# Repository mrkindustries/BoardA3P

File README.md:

BoardA3PU
=============

## Arduino-compatible FPGA board

## Schematic

## 3D views

This board was designed using kicad, you can find the CAD files in the /hardware/design folder
http://www.kicad-pcb.org

Download the schematic

[schematic.pdf](/hardware/doc/schematic.pdf?raw=true)

**Warning:** untested until the first prototype arrives

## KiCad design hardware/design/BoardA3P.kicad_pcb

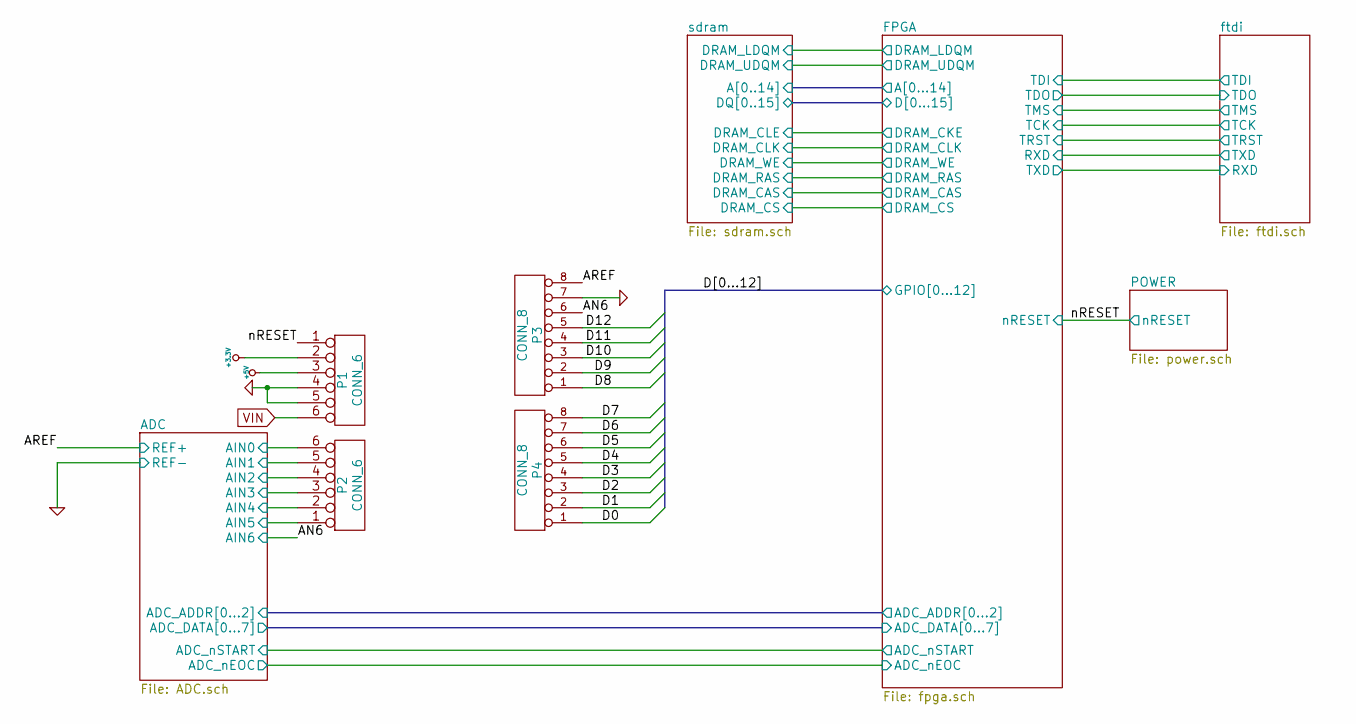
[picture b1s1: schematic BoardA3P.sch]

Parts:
P1, P2: CONN_6; SIL-6
P3, P4: CONN_8; SIL-8

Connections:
+3.3V: P1.2; also elsewhere on the board
+5V: P1.3; also elsewhere on the board
/ADC/AIN0: P2.6; also elsewhere on the board
/ADC/AIN1: P2.5; also elsewhere on the board
/ADC/AIN2: P2.4; also elsewhere on the board
/ADC/AIN3: P2.3; also elsewhere on the board
/ADC/AIN4: P2.2; also elsewhere on the board
/ADC/AIN5: P2.1; also elsewhere on the board
/ADC/AIN6: P3.6; also elsewhere on the board
/ADC/REF+: P3.8; also elsewhere on the board
/D0: P4.1; also elsewhere on the board
/D1: P4.2; also elsewhere on the board
/D2: P4.3; also elsewhere on the board
/D3: P4.4; also elsewhere on the board
/D4: P4.5; also elsewhere on the board
/D5: P4.6; also elsewhere on the board
/D6: P4.7; also elsewhere on the board
/D7: P4.8; also elsewhere on the board
/D8: P3.1; also elsewhere on the board
/D9: P3.2; also elsewhere on the board
/D10: P3.3; also elsewhere on the board
/D11: P3.4; also elsewhere on the board
/D12: P3.5; also elsewhere on the board
/FPGA/nRESET: P1.1; also elsewhere on the board
GND: P1.4, P1.5, P3.7; also elsewhere on the board
VIN: P1.6; also elsewhere on the board

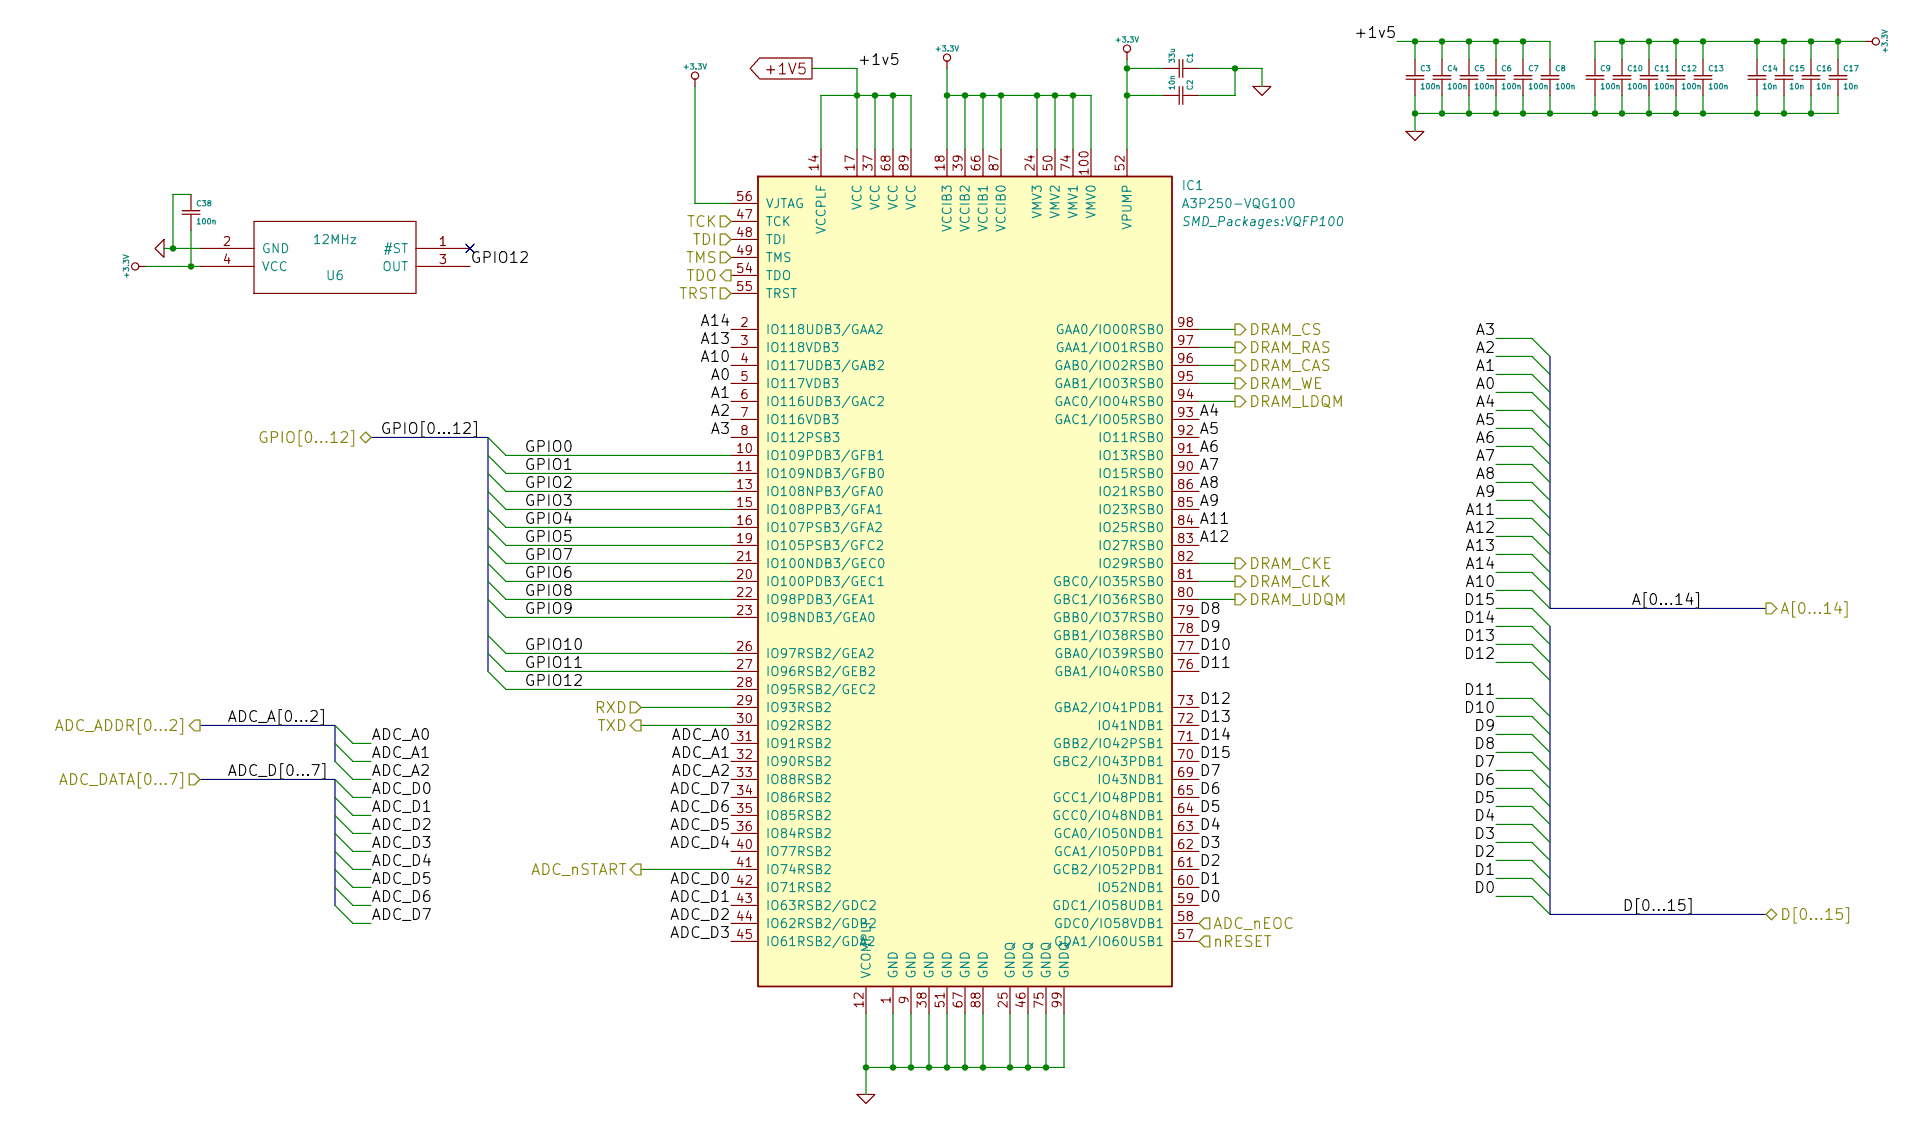
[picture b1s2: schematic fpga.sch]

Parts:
C1: 33u; c_0805
C2, C14, C15, C16, C17: 10n; c_0805
C3, C4, C5, C6, C7, C8, C9, C10, C11, C12, C13, C38: 100n; c_0805
IC1: A3P250-VQG100; VQFP100
U6: 12MHz; OSC_2x2p5

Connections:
+1V5: C3.1, C4.1, C5.1, C6.1, C7.1, C8.1, IC1.14 (VCCPLF), IC1.17 (VCC), IC1.37 (VCC), IC1.68 (VCC), IC1.89 (VCC); also elsewhere on the board
+3.3V: C1.2, C2.2, C9.1, C10.1, C11.1, C12.1, C13.1, C14.1, C15.1, C16.1, C17.1, C38.2, IC1.18 (VCCIB3), IC1.24 (VMV3), IC1.39 (VCCIB2), IC1.50 (VMV2), IC1.52 (VPUMP), IC1.56 (VJTAG), IC1.66 (VCCIB1), IC1.74 (VMV1), IC1.87 (VCCIB0), IC1.100 (VMV0), U6.4 (VCC); also elsewhere on the board
/ADC/A0: IC1.31 (IO91RSB2); also elsewhere on the board
/ADC/A1: IC1.32 (IO90RSB2); also elsewhere on the board
/ADC/A2: IC1.33 (IO88RSB2); also elsewhere on the board
/ADC/ADC_nEOC: IC1.58 (GDC0/IO58VDB1); also elsewhere on the board
/ADC/ADC_nSTART: IC1.41 (IO74RSB2); also elsewhere on the board
/D0: IC1.10 (IO109PDB3/GFB1); also elsewhere on the board
/D1: IC1.11 (IO109NDB3/GFB0); also elsewhere on the board
/D2: IC1.13 (IO108NPB3/GFA0); also elsewhere on the board
/D3: IC1.15 (IO108PPB3/GFA1); also elsewhere on the board
/D4: IC1.16 (IO107PSB3/GFA2); also elsewhere on the board
/D5: IC1.19 (IO105PSB3/GFC2); also elsewhere on the board
/D6: IC1.20 (IO100PDB3/GEC1); also elsewhere on the board
/D7: IC1.21 (IO100NDB3/GEC0); also elsewhere on the board
/D8: IC1.22 (IO98PDB3/GEA1); also elsewhere on the board
/D9: IC1.23 (IO98NDB3/GEA0); also elsewhere on the board
/D10: IC1.26 (IO97RSB2/GEA2); also elsewhere on the board
/D11: IC1.27 (IO96RSB2/GEB2); also elsewhere on the board
/D12: IC1.28 (IO95RSB2/GEC2), U6.3 (OUT); also elsewhere on the board
/FPGA/A0: IC1.5 (IO117VDB3); also elsewhere on the board
/FPGA/A1: IC1.6 (IO116UDB3/GAC2); also elsewhere on the board
/FPGA/A2: IC1.7 (IO116VDB3); also elsewhere on the board
/FPGA/A3: IC1.8 (IO112PSB3); also elsewhere on the board
/FPGA/A4: IC1.93 (GAC1/IO05RSB0); also elsewhere on the board
/FPGA/A5: IC1.92 (IO11RSB0); also elsewhere on the board
/FPGA/A6: IC1.91 (IO13RSB0); also elsewhere on the board
/FPGA/A7: IC1.90 (IO15RSB0); also elsewhere on the board
/FPGA/A8: IC1.86 (IO21RSB0); also elsewhere on the board
/FPGA/A9: IC1.85 (IO23RSB0); also elsewhere on the board
/FPGA/A10: IC1.4 (IO117UDB3/GAB2); also elsewhere on the board
/FPGA/A11: IC1.84 (IO25RSB0); also elsewhere on the board
/FPGA/A12: IC1.83 (IO27RSB0); also elsewhere on the board
/FPGA/A13: IC1.3 (IO118VDB3); also elsewhere on the board
/FPGA/A14: IC1.2 (IO118UDB3/GAA2); also elsewhere on the board
/FPGA/ADC_D0: IC1.42 (IO71RSB2); also elsewhere on the board
/FPGA/ADC_D1: IC1.43 (IO63RSB2/GDC2); also elsewhere on the board
/FPGA/ADC_D2: IC1.44 (IO62RSB2/GDB2); also elsewhere on the board
/FPGA/ADC_D3: IC1.45 (IO61RSB2/GDA2); also elsewhere on the board
/FPGA/ADC_D4: IC1.40 (IO77RSB2); also elsewhere on the board
/FPGA/ADC_D5: IC1.36 (IO84RSB2); also elsewhere on the board
/FPGA/ADC_D6: IC1.35 (IO85RSB2); also elsewhere on the board
/FPGA/ADC_D7: IC1.34 (IO86RSB2); also elsewhere on the board
/FPGA/D0: IC1.59 (GDC1/IO58UDB1); also elsewhere on the board
/FPGA/D1: IC1.60 (IO52NDB1); also elsewhere on the board
/FPGA/D2: IC1.61 (GCB2/IO52PDB1); also elsewhere on the board
/FPGA/D3: IC1.62 (GCA1/IO50PDB1); also elsewhere on the board
/FPGA/D4: IC1.63 (GCA0/IO50NDB1); also elsewhere on the board
/FPGA/D5: IC1.64 (GCC0/IO48NDB1); also elsewhere on the board
/FPGA/D6: IC1.65 (GCC1/IO48PDB1); also elsewhere on the board
/FPGA/D7: IC1.69 (IO43NDB1); also elsewhere on the board
/FPGA/D8: IC1.79 (GBB0/IO37RSB0); also elsewhere on the board
/FPGA/D9: IC1.78 (GBB1/IO38RSB0); also elsewhere on the board
/FPGA/D10: IC1.77 (GBA0/IO39RSB0); also elsewhere on the board
/FPGA/D11: IC1.76 (GBA1/IO40RSB0); also elsewhere on the board
/FPGA/D12: IC1.73 (GBA2/IO41PDB1); also elsewhere on the board
/FPGA/D13: IC1.72 (IO41NDB1); also elsewhere on the board
/FPGA/D14: IC1.71 (GBB2/IO42PSB1); also elsewhere on the board
/FPGA/D15: IC1.70 (GBC2/IO43PDB1); also elsewhere on the board
/FPGA/DRAM_CAS: IC1.96 (GAB0/IO02RSB0); also elsewhere on the board
/FPGA/DRAM_CKE: IC1.82 (IO29RSB0); also elsewhere on the board
/FPGA/DRAM_CLK: IC1.81 (GBC0/IO35RSB0); also elsewhere on the board
/FPGA/DRAM_CS: IC1.98 (GAA0/IO00RSB0); also elsewhere on the board
/FPGA/DRAM_LDQM: IC1.94 (GAC0/IO04RSB0); also elsewhere on the board
/FPGA/DRAM_RAS: IC1.97 (GAA1/IO01RSB0); also elsewhere on the board
/FPGA/DRAM_UDQM: IC1.80 (GBC1/IO36RSB0); also elsewhere on the board
/FPGA/DRAM_WE: IC1.95 (GAB1/IO03RSB0); also elsewhere on the board
/FPGA/RXD: IC1.29 (IO93RSB2); also elsewhere on the board
/FPGA/TCK: IC1.47 (TCK); also elsewhere on the board
/FPGA/TDI: IC1.48 (TDI); also elsewhere on the board
/FPGA/TDO: IC1.54 (TDO); also elsewhere on the board
/FPGA/TMS: IC1.49 (TMS); also elsewhere on the board
/FPGA/TRST: IC1.55 (TRST); also elsewhere on the board
/FPGA/nRESET: IC1.57 (GDA1/IO60USB1); also elsewhere on the board
/ftdi/RXD: IC1.30 (IO92RSB2); also elsewhere on the board
GND: C1.1, C2.1, C3.2, C4.2, C5.2, C6.2, C7.2, C8.2, C9.2, C10.2, C11.2, C12.2, C13.2, C14.2, C15.2, C16.2, C17.2, C38.1, IC1.1 (GND), IC1.9 (GND), IC1.12 (VCOMPLF), IC1.25 (GNDQ), IC1.38 (GND), IC1.46 (GNDQ), IC1.51 (GND), IC1.67 (GND), IC1.75 (GNDQ), IC1.88 (GND), IC1.99 (GNDQ), U6.2 (GND); also elsewhere on the board

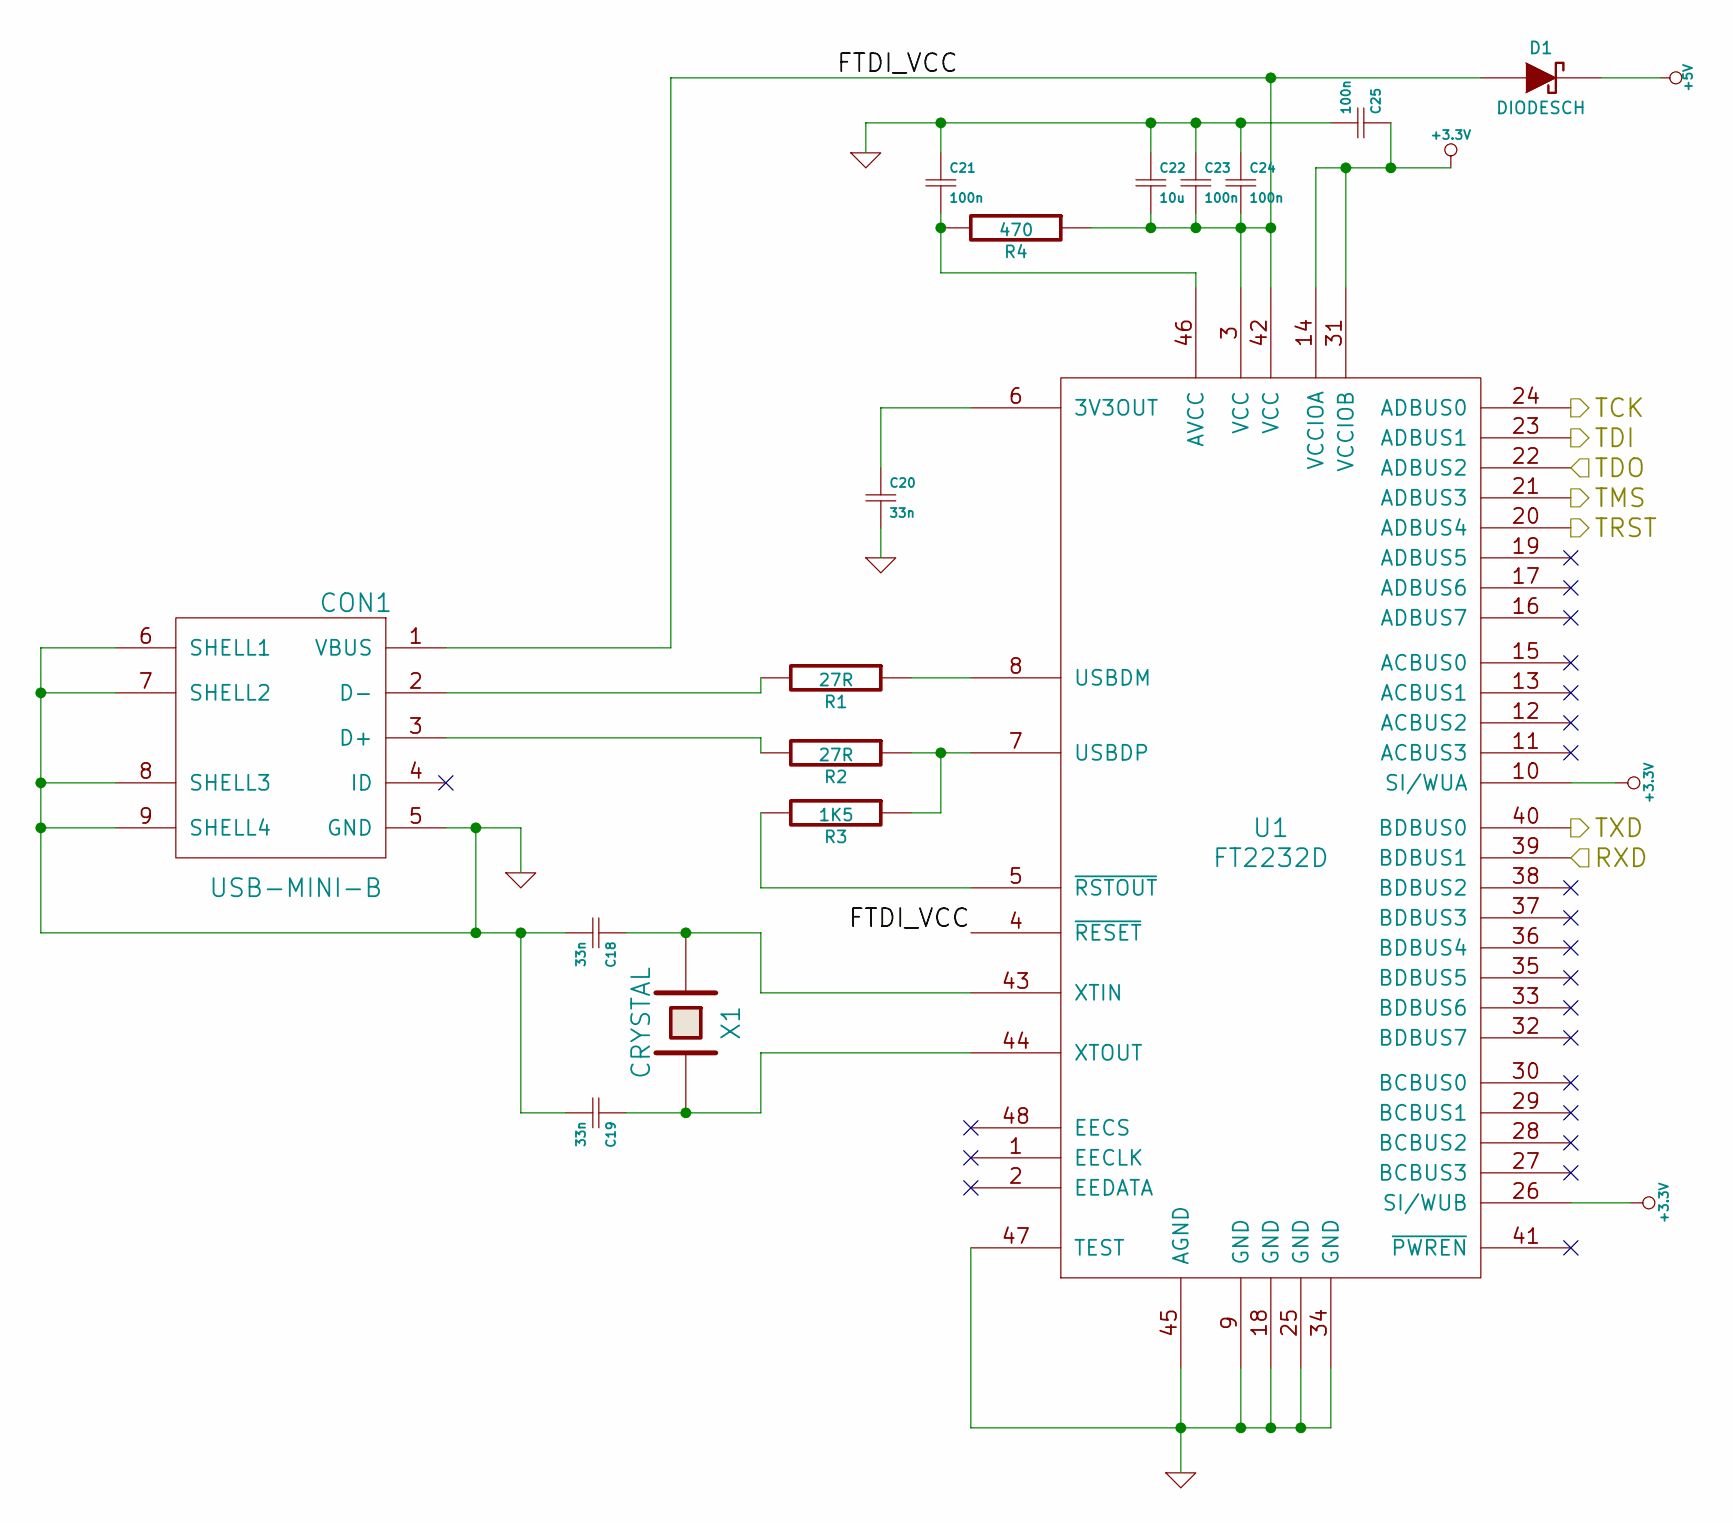
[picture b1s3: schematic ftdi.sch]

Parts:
C18, C19, C20: 33n; c_0805
C21, C23, C24, C25: 100n; c_0805
C22: 10u; c_1206
CON1: USB-MINI-B; USB_MINI_B
D1: DIODESCH; Diode-SMA_Standard
R1, R2: 27R; Resistor_SMD0805_ReflowWave
R3: 1K5; Resistor_SMD0805_ReflowWave
R4: 470; Resistor_SMD0805_ReflowWave
U1: FT2232D; lqfp-48
X1: CRYSTAL; crystal_FA238-TSX3225

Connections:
+3.3V: C25.1, U1.10 (SI/WUA), U1.14 (VCCIOA), U1.26 (SI/WUB), U1.31 (VCCIOB); also elsewhere on the board
+5V: D1.2 (K); also elsewhere on the board
/FPGA/RXD: U1.40 (BDBUS0); also elsewhere on the board
/FPGA/TCK: U1.24 (ADBUS0); also elsewhere on the board
/FPGA/TDI: U1.23 (ADBUS1); also elsewhere on the board
/FPGA/TDO: U1.22 (ADBUS2); also elsewhere on the board
/FPGA/TMS: U1.21 (ADBUS3); also elsewhere on the board
/FPGA/TRST: U1.20 (ADBUS4); also elsewhere on the board
/ftdi/FTDI_VCC: C22.2, C23.2, C24.2, CON1.1 (VBUS), D1.1 (A), R4.1, U1.3 (VCC), U1.4 (~RESET), U1.42 (VCC)
/ftdi/RXD: U1.39 (BDBUS1); also elsewhere on the board
GND: C18.2, C19.2, C20.2, C21.1, C22.1, C23.1, C24.1, C25.2, CON1.5 (GND), CON1.6 (SHELL1), CON1.7 (SHELL2), CON1.8 (SHELL3), CON1.9 (SHELL4), U1.9 (GND), U1.18 (GND), U1.25 (GND), U1.34 (GND), U1.45 (AGND), U1.47 (TEST); also elsewhere on the board
unnamed: C18.1, U1.43 (XTIN), X1.1
unnamed: C19.1, U1.44 (XTOUT), X1.2
unnamed: C20.1, U1.6 (3V3OUT)
unnamed: C21.2, R4.2, U1.46 (AVCC)
unnamed: CON1.2 (D-), R1.2
unnamed: CON1.3 (D+), R2.2
unnamed: R1.1, U1.8 (USBDM)
unnamed: R2.1, R3.1, U1.7 (USBDP)
unnamed: R3.2, U1.5 (~RSTOUT)

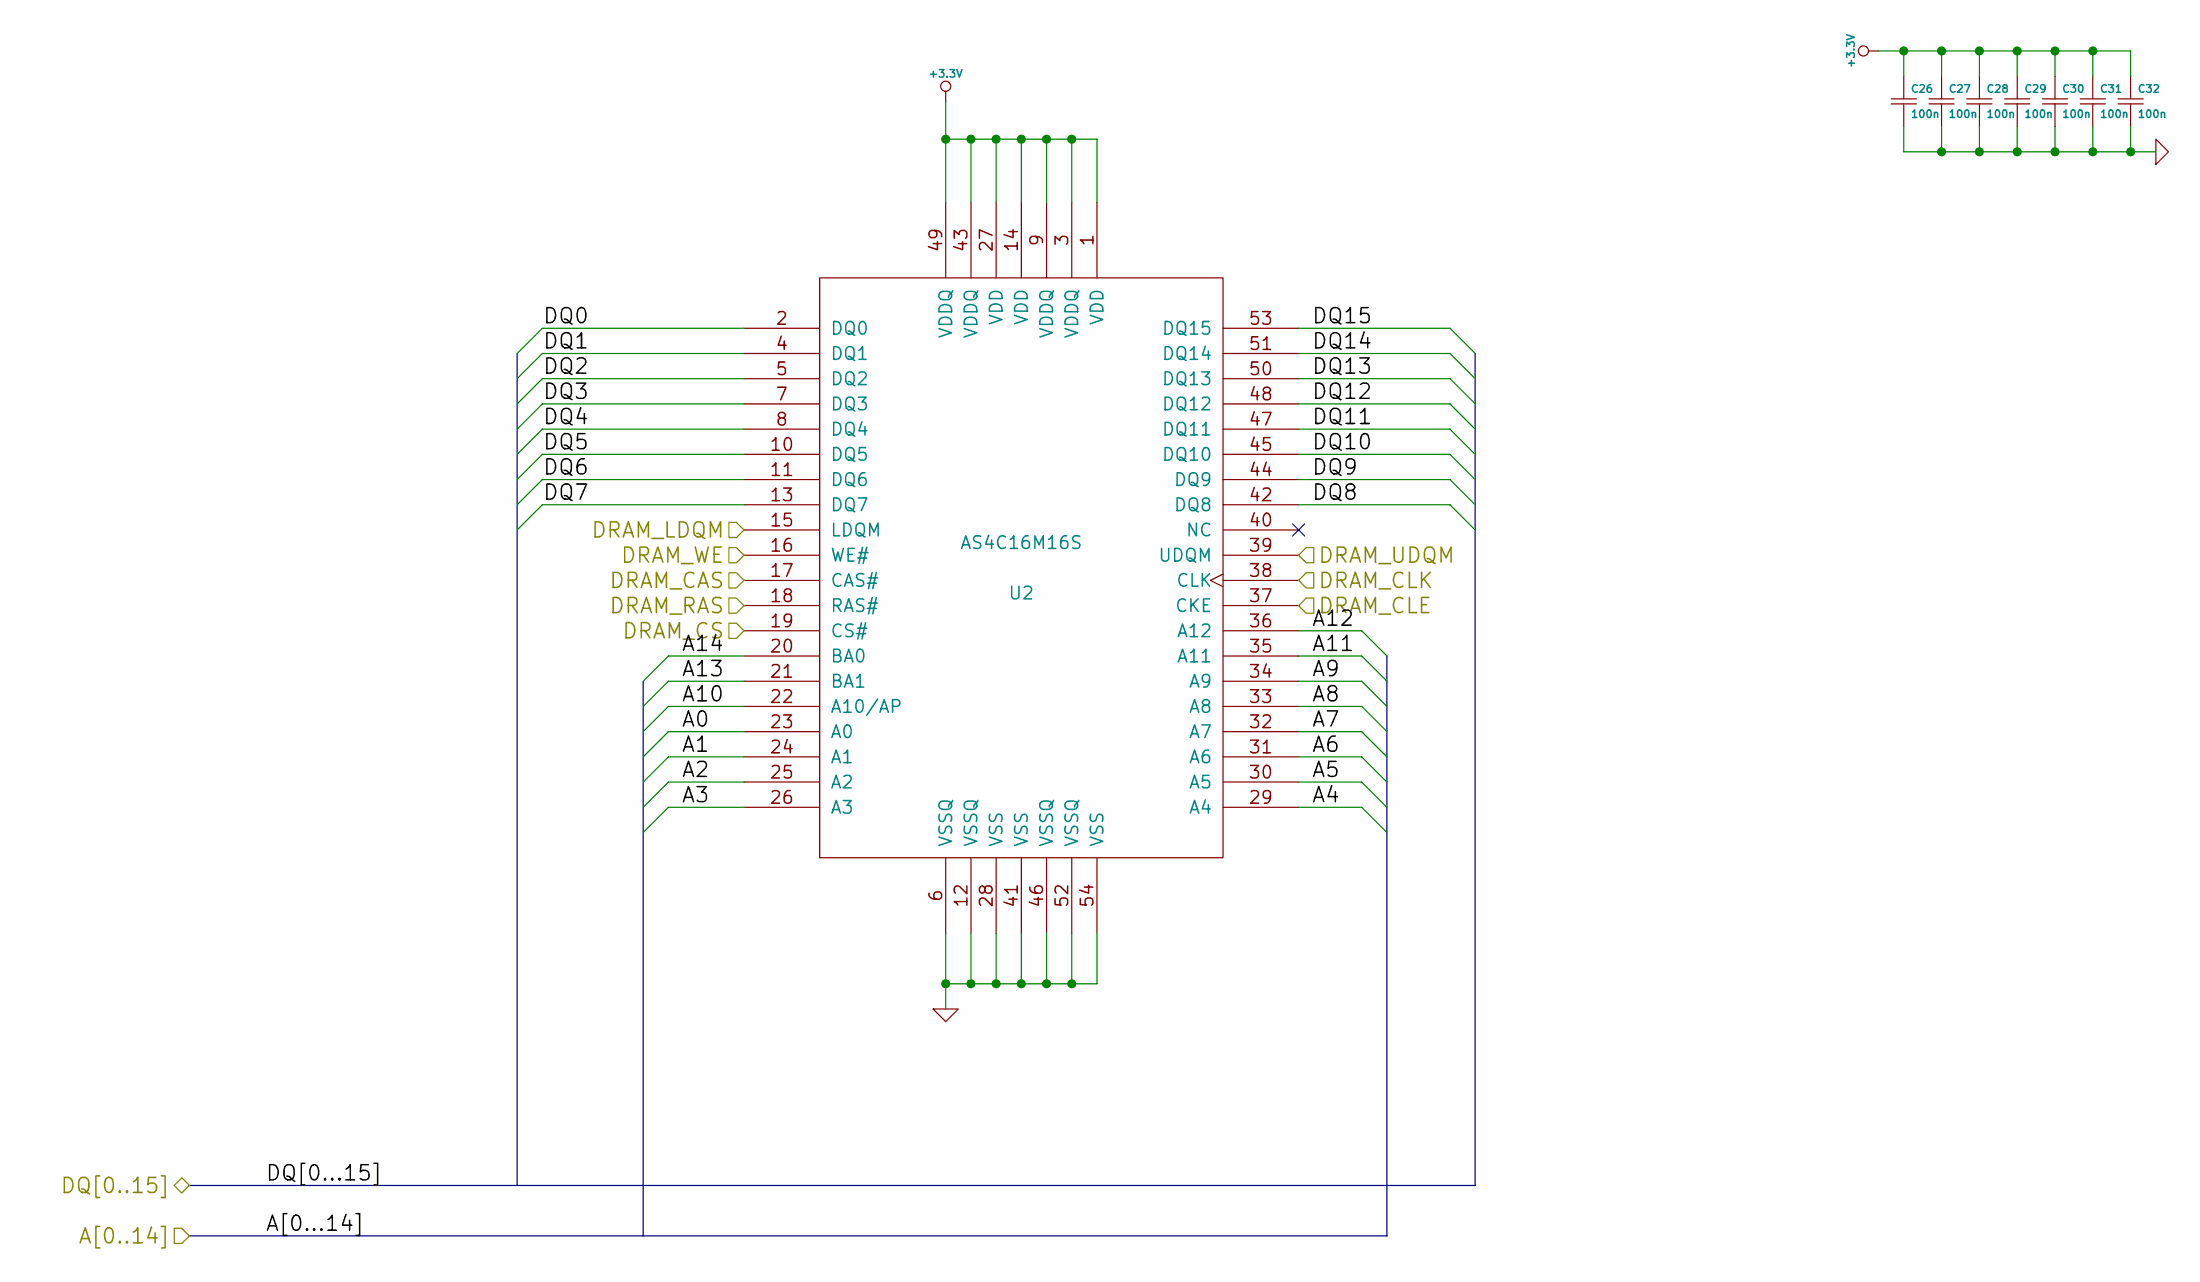
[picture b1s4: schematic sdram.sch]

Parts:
C26, C27, C28, C29, C30, C31, C32: 100n; c_0805
U2: AS4C16M16S; TSOP_II_54

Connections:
+3.3V: C26.1, C27.1, C28.1, C29.1, C30.1, C31.1, C32.1, U2.1 (VDD), U2.3 (VDDQ), U2.9 (VDDQ), U2.14 (VDD), U2.27 (VDD), U2.43 (VDDQ), U2.49 (VDDQ); also elsewhere on the board
/FPGA/A0: U2.23 (A0); also elsewhere on the board
/FPGA/A1: U2.24 (A1); also elsewhere on the board
/FPGA/A2: U2.25 (A2); also elsewhere on the board
/FPGA/A3: U2.26 (A3); also elsewhere on the board
/FPGA/A4: U2.29 (A4); also elsewhere on the board
/FPGA/A5: U2.30 (A5); also elsewhere on the board
/FPGA/A6: U2.31 (A6); also elsewhere on the board
/FPGA/A7: U2.32 (A7); also elsewhere on the board
/FPGA/A8: U2.33 (A8); also elsewhere on the board
/FPGA/A9: U2.34 (A9); also elsewhere on the board
/FPGA/A10: U2.22 (A10/AP); also elsewhere on the board
/FPGA/A11: U2.35 (A11); also elsewhere on the board
/FPGA/A12: U2.36 (A12); also elsewhere on the board
/FPGA/A13: U2.21 (BA1); also elsewhere on the board
/FPGA/A14: U2.20 (BA0); also elsewhere on the board
/FPGA/D0: U2.2 (DQ0); also elsewhere on the board
/FPGA/D1: U2.4 (DQ1); also elsewhere on the board
/FPGA/D2: U2.5 (DQ2); also elsewhere on the board
/FPGA/D3: U2.7 (DQ3); also elsewhere on the board
/FPGA/D4: U2.8 (DQ4); also elsewhere on the board
/FPGA/D5: U2.10 (DQ5); also elsewhere on the board
/FPGA/D6: U2.11 (DQ6); also elsewhere on the board
/FPGA/D7: U2.13 (DQ7); also elsewhere on the board
/FPGA/D8: U2.42 (DQ8); also elsewhere on the board
/FPGA/D9: U2.44 (DQ9); also elsewhere on the board
/FPGA/D10: U2.45 (DQ10); also elsewhere on the board
/FPGA/D11: U2.47 (DQ11); also elsewhere on the board
/FPGA/D12: U2.48 (DQ12); also elsewhere on the board
/FPGA/D13: U2.50 (DQ13); also elsewhere on the board
/FPGA/D14: U2.51 (DQ14); also elsewhere on the board
/FPGA/D15: U2.53 (DQ15); also elsewhere on the board
/FPGA/DRAM_CAS: U2.17 (CAS#); also elsewhere on the board
/FPGA/DRAM_CKE: U2.37 (CKE); also elsewhere on the board
/FPGA/DRAM_CLK: U2.38 (CLK); also elsewhere on the board
/FPGA/DRAM_CS: U2.19 (CS#); also elsewhere on the board
/FPGA/DRAM_LDQM: U2.15 (LDQM); also elsewhere on the board
/FPGA/DRAM_RAS: U2.18 (RAS#); also elsewhere on the board
/FPGA/DRAM_UDQM: U2.39 (UDQM); also elsewhere on the board
/FPGA/DRAM_WE: U2.16 (WE#); also elsewhere on the board
GND: C26.2, C27.2, C28.2, C29.2, C30.2, C31.2, C32.2, U2.6 (VSSQ), U2.12 (VSSQ), U2.28 (VSS), U2.41 (VSS), U2.46 (VSSQ), U2.52 (VSSQ), U2.54 (VSS); also elsewhere on the board

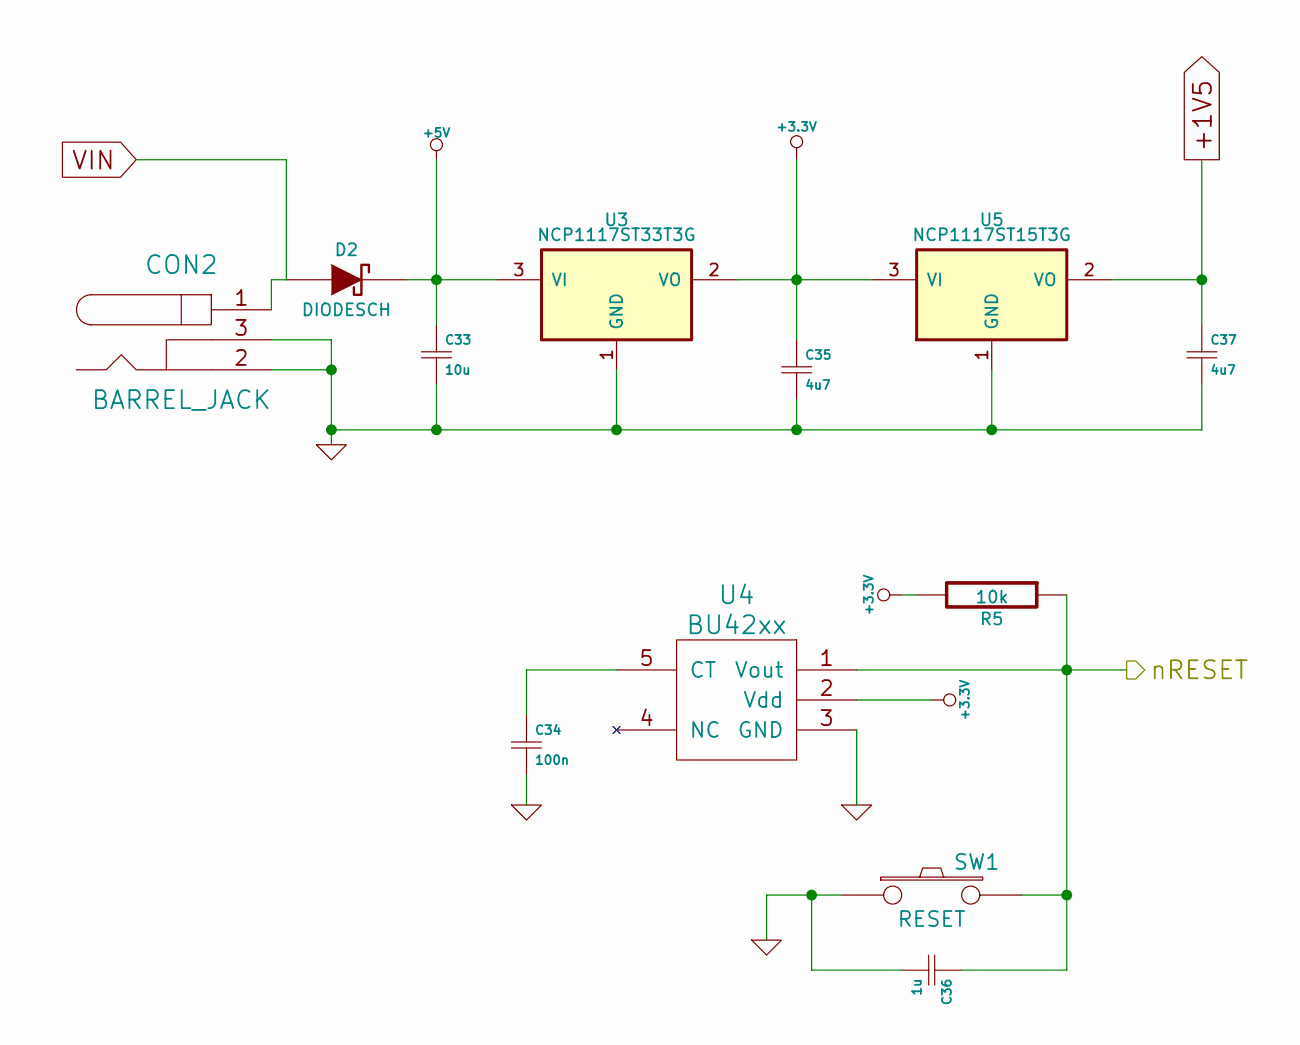
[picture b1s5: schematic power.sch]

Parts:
C33: 10u; c_1206
C34: 100n; c_0805
C35, C37: 4u7; c_1206
C36: 1u; c_0805
CON2: BARREL_JACK
D2: DIODESCH; Diode-SMA_Standard
R5: 10k; Resistor_SMD0805_ReflowWave
SW1: RESET; smd_push
U3: NCP1117ST33T3G; DPAK2
U4: BU42xx; SSOP-5
U5: NCP1117ST15T3G; DPAK2

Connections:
+1V5: C37.1, U5.2 (VO); also elsewhere on the board
+3.3V: C35.1, R5.2, U3.2 (VO), U4.2 (Vdd), U5.3 (VI); also elsewhere on the board
+5V: C33.1, D2.2 (K), U3.3 (VI); also elsewhere on the board
/FPGA/nRESET: C36.1, R5.1, SW1.2, U4.1 (Vout); also elsewhere on the board
GND: C33.2, C34.2, C35.2, C36.2, C37.2, CON2.2, CON2.3, SW1.1, U3.1 (GND), U4.3 (GND), U5.1 (GND); also elsewhere on the board
unnamed: C34.1, U4.5 (CT)
VIN: CON2.1, D2.1 (A); also elsewhere on the board

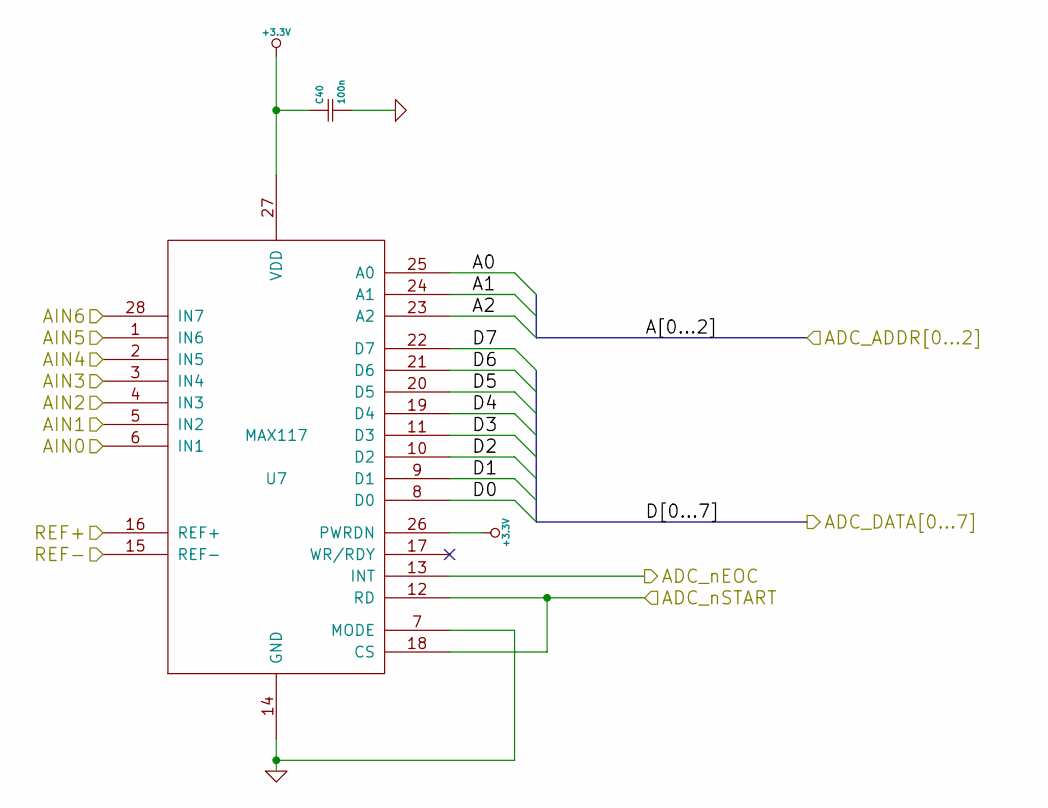
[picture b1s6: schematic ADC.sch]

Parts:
C40: 100n; c_0805
U7: MAX117; SSOP28

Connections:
+3.3V: C40.1, U7.26 (PWRDN), U7.27 (VDD); also elsewhere on the board
/ADC/A0: U7.25 (A0); also elsewhere on the board
/ADC/A1: U7.24 (A1); also elsewhere on the board
/ADC/A2: U7.23 (A2); also elsewhere on the board
/ADC/ADC_nEOC: U7.13 (INT); also elsewhere on the board
/ADC/ADC_nSTART: U7.12 (RD), U7.18 (CS); also elsewhere on the board
/ADC/AIN0: U7.6 (IN1); also elsewhere on the board
/ADC/AIN1: U7.5 (IN2); also elsewhere on the board
/ADC/AIN2: U7.4 (IN3); also elsewhere on the board
/ADC/AIN3: U7.3 (IN4); also elsewhere on the board
/ADC/AIN4: U7.2 (IN5); also elsewhere on the board
/ADC/AIN5: U7.1 (IN6); also elsewhere on the board
/ADC/AIN6: U7.28 (IN7); also elsewhere on the board
/ADC/REF+: U7.16 (REF+); also elsewhere on the board
/FPGA/ADC_D0: U7.8 (D0); also elsewhere on the board
/FPGA/ADC_D1: U7.9 (D1); also elsewhere on the board
/FPGA/ADC_D2: U7.10 (D2); also elsewhere on the board
/FPGA/ADC_D3: U7.11 (D3); also elsewhere on the board
/FPGA/ADC_D4: U7.19 (D4); also elsewhere on the board
/FPGA/ADC_D5: U7.20 (D5); also elsewhere on the board
/FPGA/ADC_D6: U7.21 (D6); also elsewhere on the board
/FPGA/ADC_D7: U7.22 (D7); also elsewhere on the board
GND: C40.2, U7.7 (MODE), U7.14 (GND), U7.15 (REF-); also elsewhere on the board

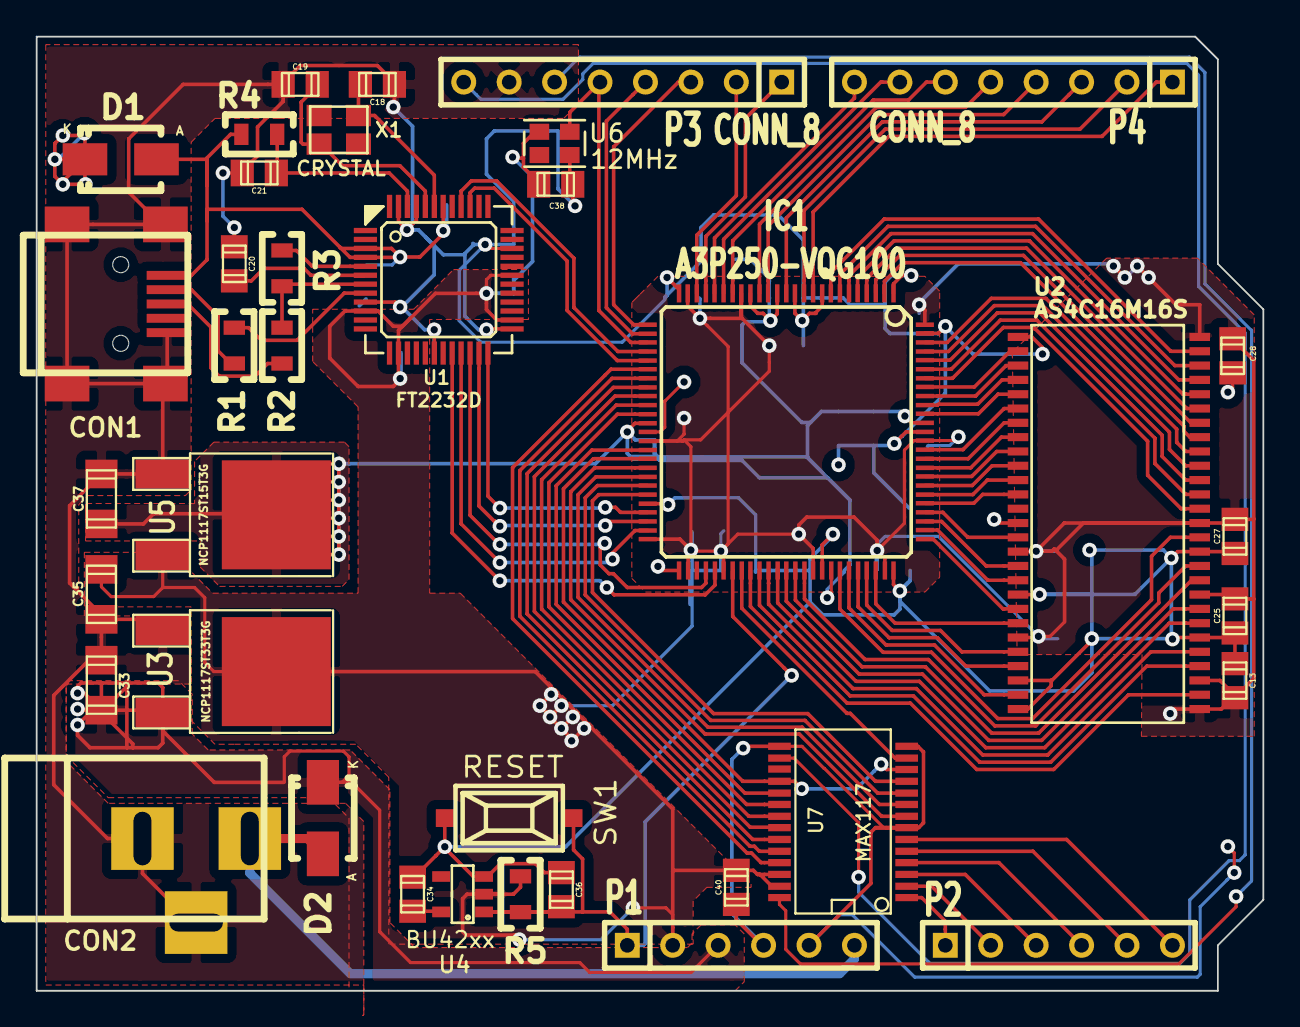
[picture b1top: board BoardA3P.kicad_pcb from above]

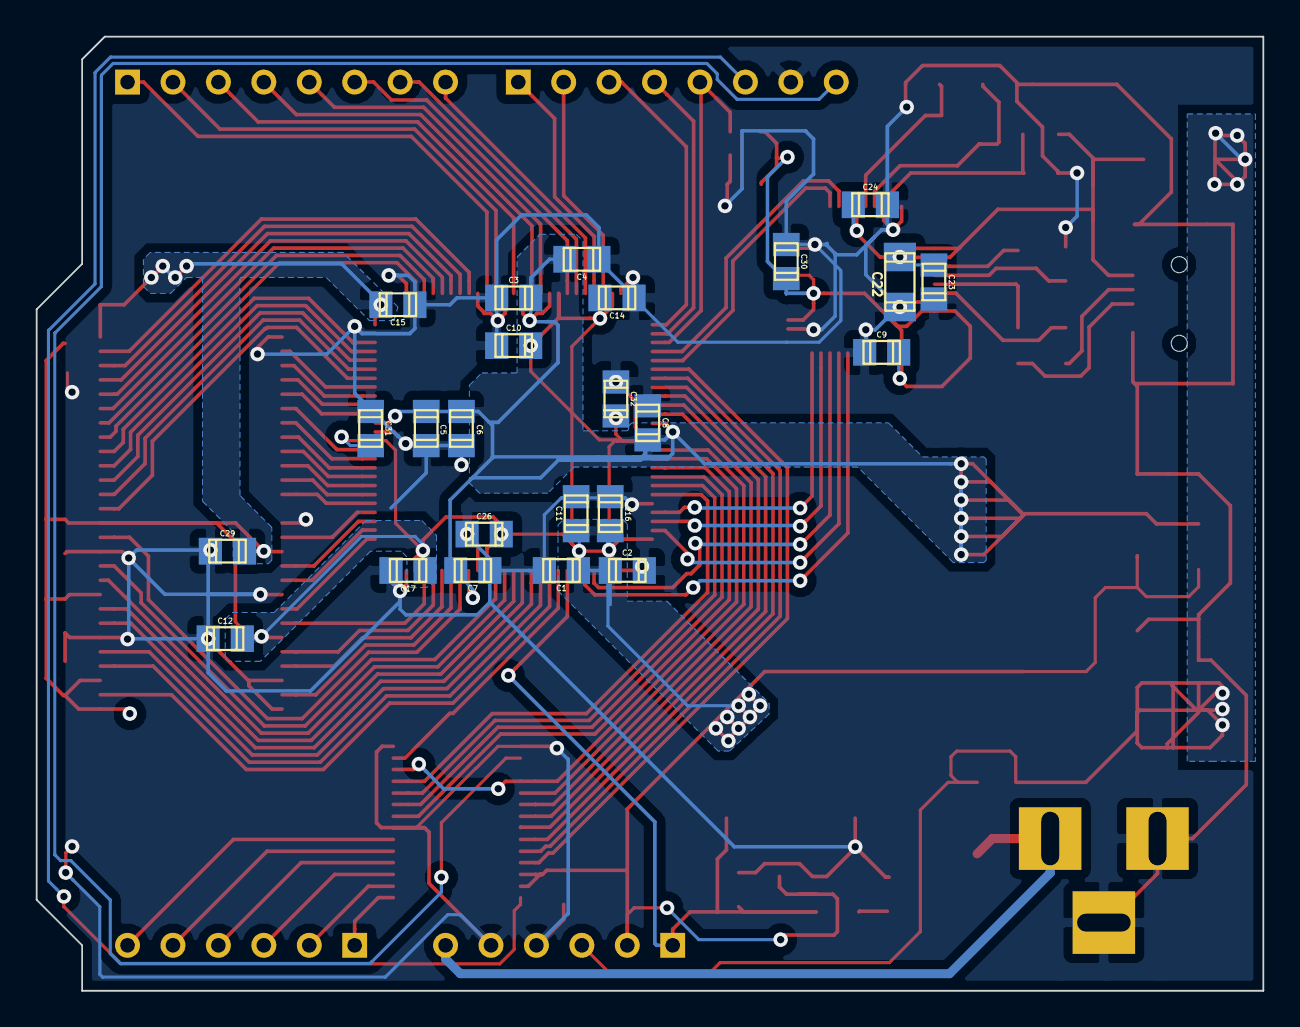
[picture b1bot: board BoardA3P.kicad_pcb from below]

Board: 2 copper layers, 68.6 x 53.3 mm, 62 parts (24 on the bottom side), 97 nets.

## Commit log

2015-03-25 First automated commit of the project
2015-03-25 Added hardware design files (schematic + layout)
2015-03-30 Added readme and a couple of images
2015-04-02 Added LEDs, smaller SDRAM
